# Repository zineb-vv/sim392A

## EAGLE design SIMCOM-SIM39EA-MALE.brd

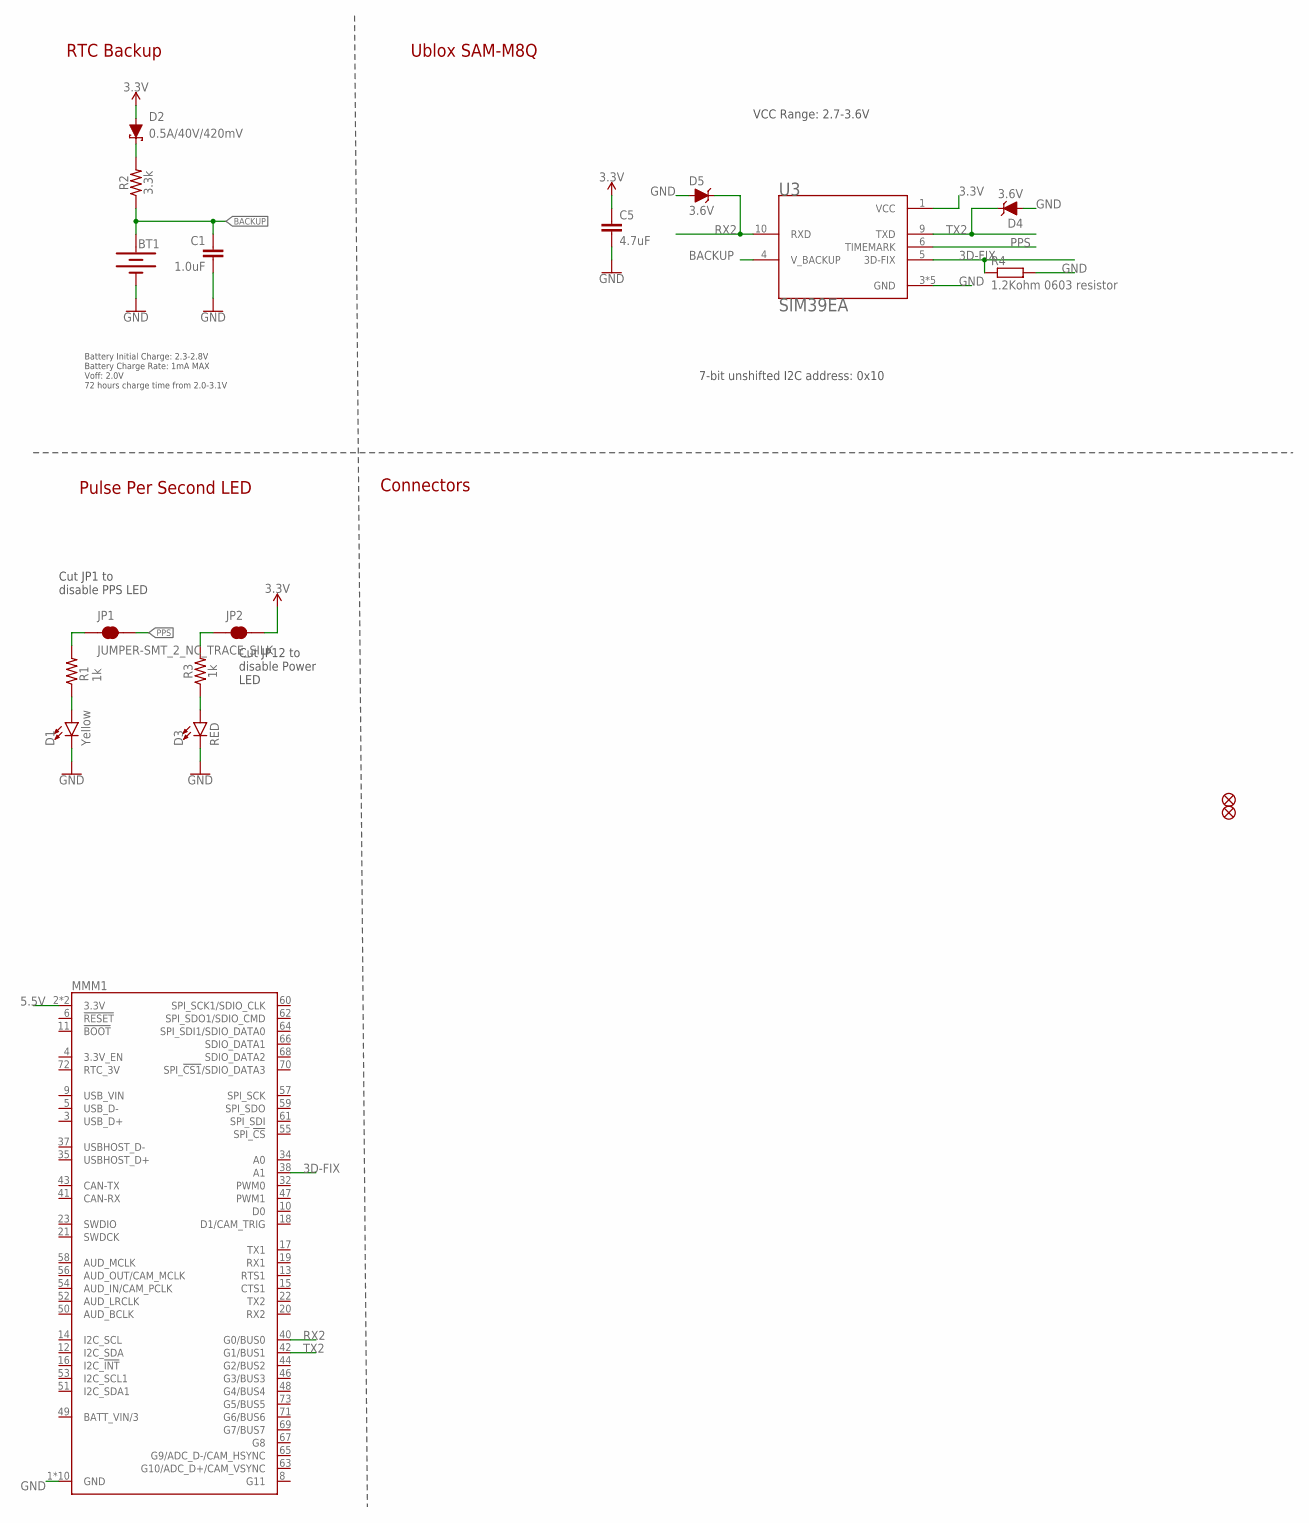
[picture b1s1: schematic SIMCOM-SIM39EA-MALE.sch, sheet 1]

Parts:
BT1: 6.8MM_COIN_CELL; ML414H_IV01E
C1: 1.0uF; 0603
C5: 4.7uF; 0402-TIGHT
D1: Yellow; LED-0603
D2: 0.5A/40V/420mV; SOD-323
D3: RED; LED-0603
D4, D5: 3.6V; SOD-323
FD3, FD4: FIDUCIALUFIDUCIAL; FIDUCIAL-MICRO
JP1, JP2: JUMPER-SMT_2_NC_TRACE_SILK; SMT-JUMPER_2_NC_TRACE_SILK
MMM1: MICROMOD_4222_MALE
R1, R3: 1k; 0603
R2: 3.3k; 0603
R4: 1.2Kohm 0603 resistor; R603
U3: SIM39EA; DFN1600X1600X750-13N

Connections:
3.3V: C5.1, D2.A, JP2.2, U3.1 (VCC); also elsewhere on the board
3D-FIX: MMM1.38 (A1), R4.1, U3.5 (3D-FIX)
5.5V: MMM1.2 (3.3V), MMM1.74 (3.3V); also elsewhere on the board
BACKUP: BT1.+, C1.1, R2.1, U3.4 (V_BACKUP)
GND: BT1.-, C1.2, C5.2, D1.C, D3.C, D4.A, D5.A, MMM1.1 (GND), MMM1.7 (GND), MMM1.33 (GND), MMM1.36 (GND), MMM1.39 (GND), MMM1.45 (GND), MMM1.75 (GND), MMM1.GND1 (GND), MMM1.GND2 (GND), MMM1.GND3 (GND), R4.2, U3.3 (GND), U3.8 (GND), U3.11 (GND), U3.12 (GND), U3.13 (GND); also elsewhere on the board
unnamed: JP2.1, R3.2
unnamed: D1.A, R1.1
unnamed: D3.A, R3.1
unnamed: JP1.1, R1.2
unnamed: D2.C, R2.2
PPS: JP1.2, U3.6 (TIMEMARK)
RX2: D5.C, MMM1.40 (G0/BUS0), U3.10 (RXD)
TX2: D4.C, MMM1.42 (G1/BUS1), U3.9 (TXD)

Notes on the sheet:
7-bit unshifted I2C address: 0x10
Ublox SAM-M8Q
RTC Backup
Pulse Per Second LED
Cut JP1 to disable PPS LED
Connectors
Cut JP12 to disable Power LED
VCC Range: 2.7-3.6V
Battery Initial Charge: 2.3-2.8V Battery Charge Rate: 1mA MAX Voff: 2.0V 72 hours charge time from 2.0-3.1V

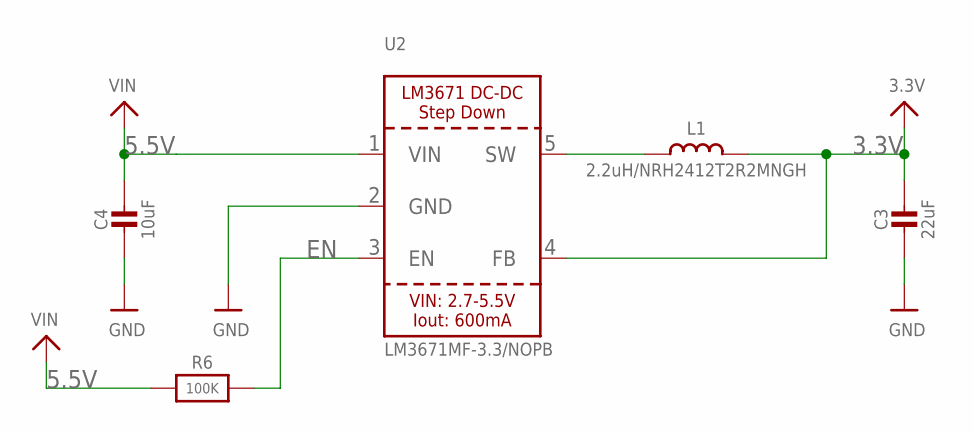
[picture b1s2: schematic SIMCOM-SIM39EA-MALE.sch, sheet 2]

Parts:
C3: 22uF; 0805-NO
C4: 10uF; 0805-NO
L1: 2.2uH/NRH2412T2R2MNGH; INDUCTOR_TAIYOYUDEN_NRH2412T
R6: 100K; 0805-NO
U2: LM3671MF-3.3/NOPB; SOT23-5

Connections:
3.3V: C3.1, L1.2, U2.4 (FB); also elsewhere on the board
5.5V: C4.1, R6.1, U2.1 (VIN); also elsewhere on the board
EN: R6.2, U2.3 (EN)
GND: C3.2, C4.2, U2.2 (GND); also elsewhere on the board
unnamed: L1.1, U2.5 (SW)

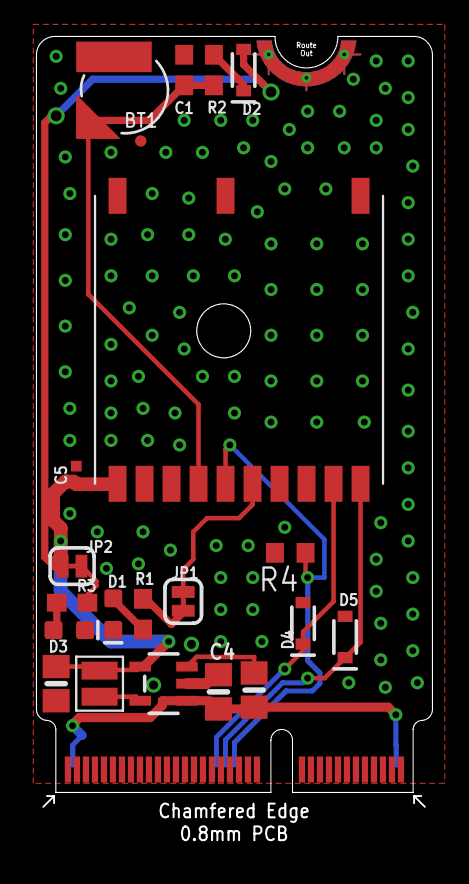
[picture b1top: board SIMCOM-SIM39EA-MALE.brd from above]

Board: 2 copper layers, 21.9 x 45.0 mm, 23 parts (1 on the bottom side), 15 nets.

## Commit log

2021-01-26 Create ...

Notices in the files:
parts and their libraries:
SparkFun-Resistors: Licensing: Creative Commons ShareAlike 4.0 International - https://creativecommons.org/licenses/by-sa/4.0
microbuilder: This work is placed in the public domain, and may be freely used for commercial and non-commercial work with the following conditions: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
